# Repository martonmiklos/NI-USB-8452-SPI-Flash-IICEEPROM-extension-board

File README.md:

# NI USB-8452 SPI Flash/IIC EEPROM extension board
This is a small extension board which could be used to program I2C EEPROMs or SPI flashes with the [National Instrument's USB-8452](http://www.ni.com/hu-hu/support/model.usb-8452.html)
Drawn in EAGLE 6.x back in the days when I worked for NI to acts as a placeholder on a 100*100 ditypcb order. I still have a couple of bare PCBs let me know if you are interested in one. 

## Features:
* Footprint for soldering narrow/wide SPI flashes (WP, HOLD pulled high)
* Footprint for I2C eeproms
* VCC for bothc chips could be jumper selected from the VREF or the +5V from the 
* AVR ISP pinout connector

## Missing features:
* LED

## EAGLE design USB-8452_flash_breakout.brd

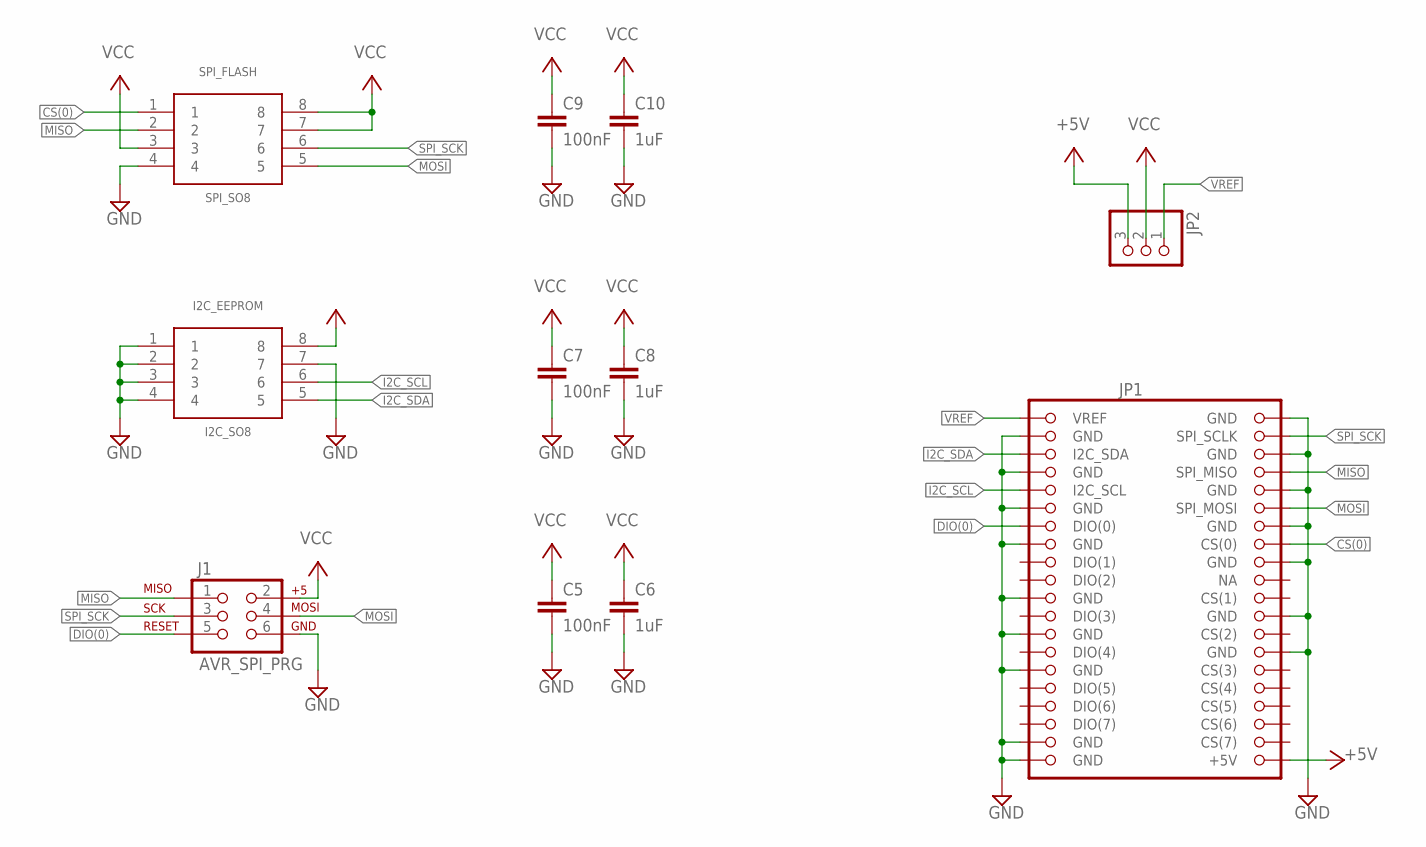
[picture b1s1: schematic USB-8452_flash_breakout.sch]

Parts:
C5, C7, C9: 100nF; C0603
C6, C8, C10: 1uF; C0603
I2C_EEPROM: I2C_SO8; SO8_LONG
J1: AVR_SPI_PRG; 2X3-NS
JP1: USB8452_HEADER; 2X20
JP2: PINHD-1X3; 1X03
SPI_FLASH: SPI_SO8; SO8_LONG

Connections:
+5V: JP1.40 (+5V), JP2.3
CS(0): JP1.16 (CS(0)), SPI_FLASH.1
DIO(0): J1.5, JP1.13 (DIO(0))
GND: C5.2, C6.2, C7.2, C8.2, C9.2, C10.2, I2C_EEPROM.1, I2C_EEPROM.2, I2C_EEPROM.3, I2C_EEPROM.4, I2C_EEPROM.7, J1.6, JP1.2 (GND), JP1.3 (GND), JP1.6 (GND), JP1.7 (GND), JP1.10 (GND), JP1.11 (GND), JP1.14 (GND), JP1.15 (GND), JP1.18 (GND), JP1.21 (GND), JP1.24 (GND), JP1.25 (GND), JP1.28 (GND), JP1.29 (GND), JP1.37 (GND), JP1.39 (GND), SPI_FLASH.4
I2C_SCL: I2C_EEPROM.6, JP1.9 (I2C_SCL)
I2C_SDA: I2C_EEPROM.5, JP1.5 (I2C_SDA)
MISO: J1.1, JP1.8 (SPI_MISO), SPI_FLASH.2
MOSI: J1.4, JP1.12 (SPI_MOSI), SPI_FLASH.5
SPI_SCK: J1.3, JP1.4 (SPI_SCLK), SPI_FLASH.6
VCC: C5.1, C6.1, C7.1, C8.1, C9.1, C10.1, I2C_EEPROM.8, J1.2, JP2.2, SPI_FLASH.3, SPI_FLASH.7, SPI_FLASH.8
VREF: JP1.1 (VREF), JP2.1

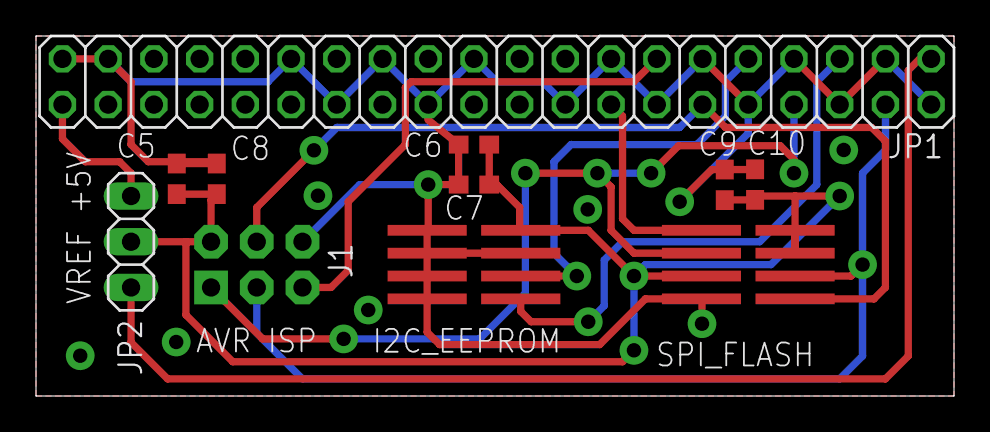
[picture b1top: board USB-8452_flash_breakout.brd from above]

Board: 2 copper layers, 51.0 x 20.0 mm, 11 parts (0 on the bottom side), 11 nets.

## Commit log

2018-01-14 - Initial add
2018-01-14 Added layout.png

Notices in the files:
parts and their libraries:
SparkFun: Licensing: CC v3.0 Share-Alike You are welcome to use this library for commercial purposes.
